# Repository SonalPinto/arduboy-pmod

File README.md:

# Arduboy PMOD

A simple dual PMOD connector board using thru-hole components on a 2-layer PCB. It was designed for playing the Arduboy on the [iCEBreaker FPGA Board](https://1bitsquared.com/products/icebreaker), but is generic enough for other creative purposes.

# Hardware Specifications

* Adafruit monochrome [1.3" 128x64 OLED](https://www.adafruit.com/product/938).
* Six 6x6mm Tactile switches. I prefer feel of the [B3F-1020](https://www.digikey.com/product-detail/en/omron-electronics-inc-emc-div/B3F-1020/SW402-ND/44059) with 100gf actuation. 10K pull down resistors for each button.
* Small Piezo speaker (like [this one](https://www.digikey.com/product-detail/en/tdk-corporation/PS1240P02CT3/445-5229-1-ND/2179635) or [this](https://www.digikey.com/product-detail/en/murata-electronics/PKM13EPYH4000-A0/490-4698-1-ND/1219329)). A [C1815 transistor](https://www.digikey.com/product-detail/en/on-semiconductor/KSC1815YTA/KSC1815YTACT-ND/3908203) and two 1K resistors for driving it.
* Generic 100mil 6x2 angled male headers like [these](https://www.digikey.com/product-detail/en/sullins-connector-solutions/PREC006DBAN-M71RC/S2112EC-06-ND/2775648) (12 position, 2 rows), for the PMOD connectors.
* The resistors are 1/8W (the distance between the pads is 200mil), instead of the bigger 1/4W ones. Links: [1K](https://www.digikey.com/product-detail/en/stackpole-electronics-inc/CF18JT1K00/CF18JT1K00CT-ND/2022742), [10K](https://www.digikey.com/product-detail/en/stackpole-electronics-inc/CF18JT10K0/CF18JT10K0CT-ND/2022766).

# Ordering

[v0.1 hosted on OSHPark](https://oshpark.com/shared_projects/jLNBtxrI)

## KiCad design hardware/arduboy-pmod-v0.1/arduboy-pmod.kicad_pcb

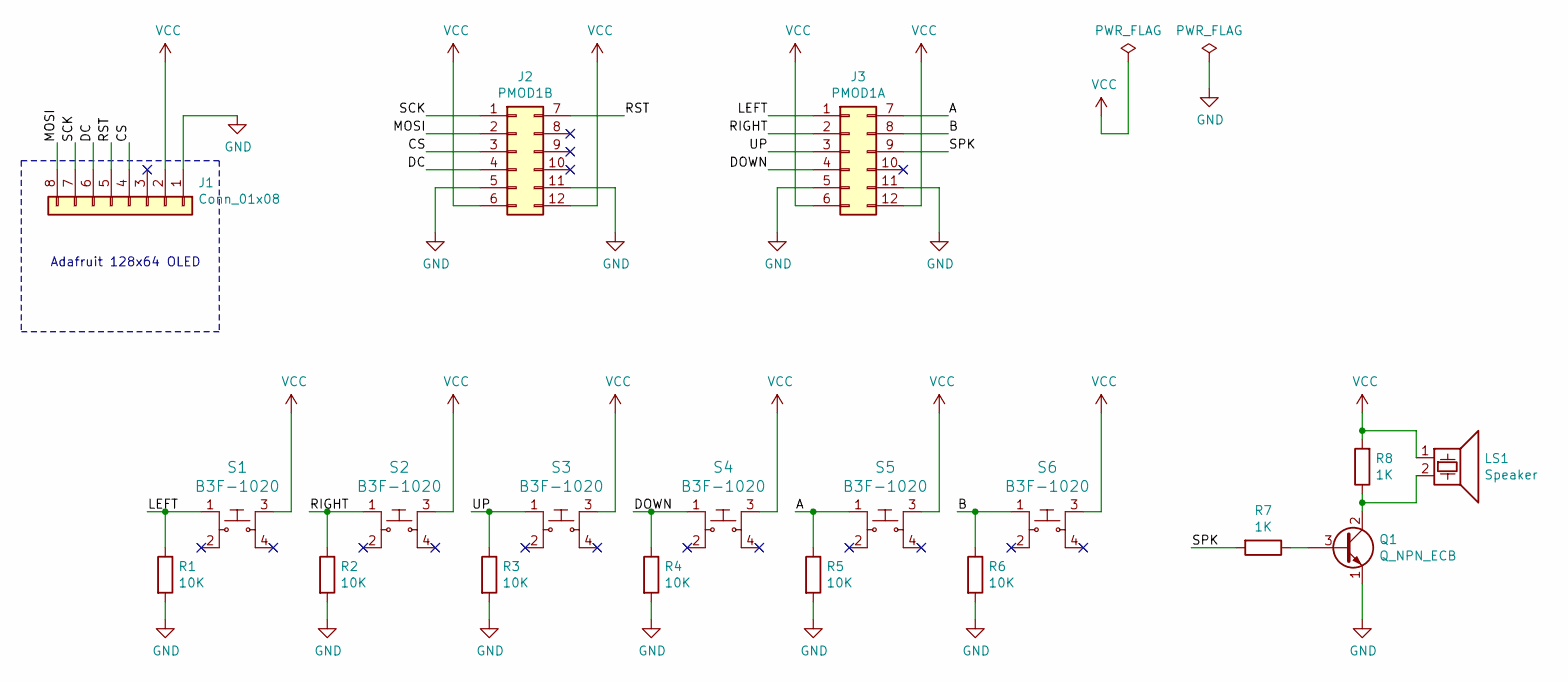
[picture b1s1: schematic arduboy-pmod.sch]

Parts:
J1: Conn_01x08; Adafruit_SSD1306
J2: PMOD1B; PMODHeader_2x6_2.54mm_Horizontal_Mirrored
J3: PMOD1A; PMODHeader_2x6_2.54mm_Horizontal_Mirrored
LS1: Speaker; Piezo_Transducer_THT_PS1240P02BT
Q1: Q_NPN_ECB; TO-92-3_Formed_Leads
R1, R2, R3, R4, R5, R6: 10K; R_Axial_DIN0204_L3.6mm_D1.6mm_P5.08mm_Horizontal
R7, R8: 1K; R_Axial_DIN0204_L3.6mm_D1.6mm_P5.08mm_Horizontal
S1, S2, S3, S4, S5, S6: B3F-1020; Switch_Tactile_THT_B3F-1xxx_nosilk; MPN B3F-1000; Digi-Key_PN SW400-ND

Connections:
/A: J3.7, R5.1, S5.1
/B: J3.8, R6.1, S6.1
/CS: J1.4, J2.3
/DC: J1.6, J2.4
/DOWN: J3.4, R4.1, S4.1
/LEFT: J3.1, R1.1, S1.1
/MOSI: J1.8, J2.2
/RIGHT: J3.2, R2.1, S2.1
/RST: J1.5, J2.7
/SCK: J1.7, J2.1
/SPK: J3.9, R7.2
/UP: J3.3, R3.1, S3.1
GND: J1.1, J2.5, J2.11, J3.5, J3.11, Q1.1 (E), R1.2, R2.2, R3.2, R4.2, R5.2, R6.2
unnamed: LS1.2, Q1.2 (C), R8.1
unnamed: Q1.3 (B), R7.1
VCC: J1.2, J2.6, J2.12, J3.6, J3.12, LS1.1, R8.2, S1.3, S2.3, S3.3, S4.3, S5.3, S6.3

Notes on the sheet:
Adafruit 128x64 OLED

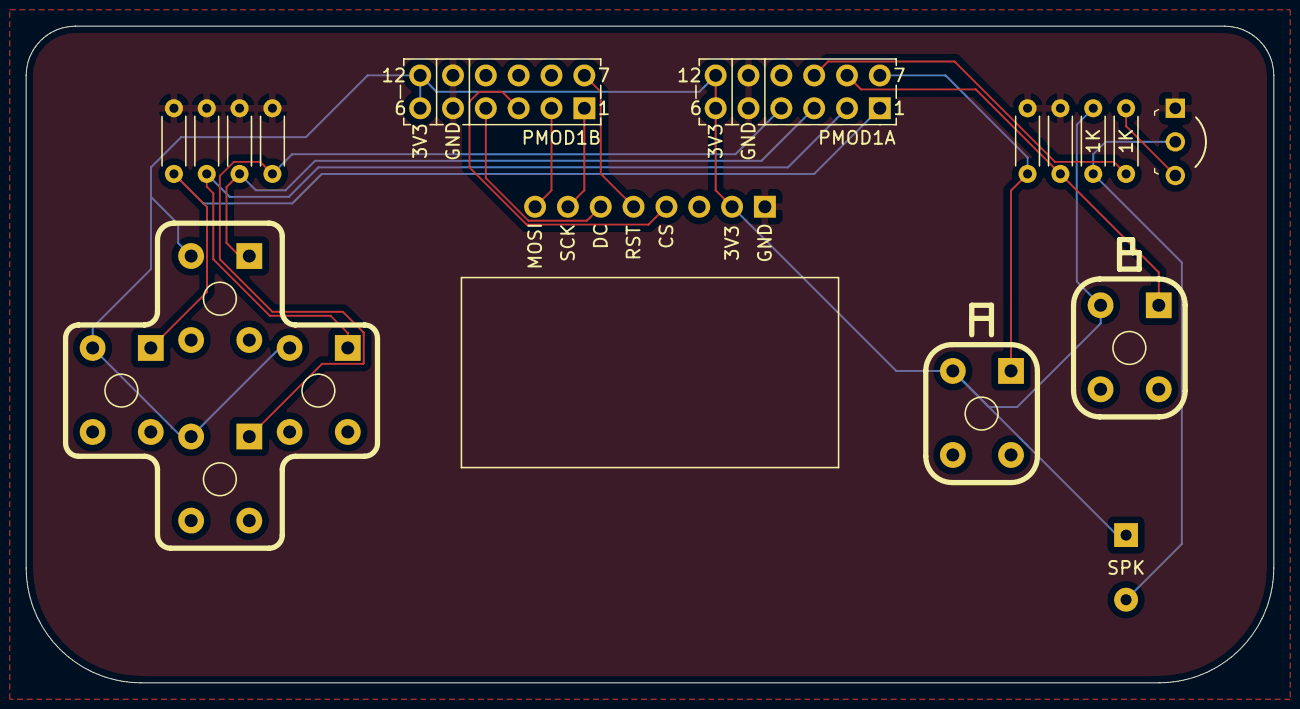
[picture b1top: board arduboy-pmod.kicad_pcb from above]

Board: 2 copper layers, 96.5 x 50.8 mm, 19 parts (0 on the bottom side), 16 nets.

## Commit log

2020-05-29 v0.1
    - PMOD kicad lib
    - v0.1 schematic and layout

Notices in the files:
hardware/arduboy-pmod-v0.1/arduboy-pmod.kicad_pcb:
License: CC-BY-SA V4.0
hardware/arduboy-pmod-v0.1/arduboy-pmod.sch:
Copyright (c) 2020 Sonal Pinto, sonalpinto@gmail.com
License: C-BY-SA V4.0
